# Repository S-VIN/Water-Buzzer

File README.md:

# Water-Buzzer
 гит проекта системы оповещения о сухости почвы.

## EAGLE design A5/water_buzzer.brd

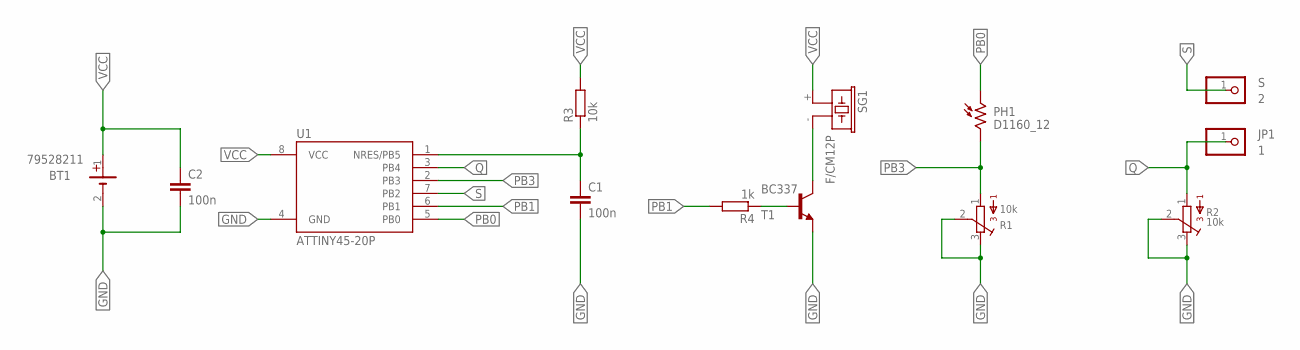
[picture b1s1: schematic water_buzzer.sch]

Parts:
BT1: 79528211
C1, C2: 100n; C5B2.5
JP1: 1; 1X01
PH1: D1160_12; D11XX
R1, R2: 10k; 3362H
R3: 10k; 0204/7
R4: 1k; 0204/7
S: 2; 1X01
SG1: F/CM12P
T1: BC337; TO92
U1: ATTINY45-20P; PDIP08_300MIL

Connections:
GND: BT1.2 (-), C1.2, C2.2, R1.2, R1.3, R2.2, R2.3, T1.1 (E), U1.4 (GND)
unnamed: C1.1, R3.1, U1.1 (NRES/PB5)
unnamed: SG1.- (2), T1.3 (C)
unnamed: R4.1, T1.2 (B)
PB0: PH1.1, U1.5 (PB0)
PB1: R4.2, U1.6 (PB1)
PB3: PH1.2, R1.1, U1.2 (PB3)
Q: JP1.1, R2.1, U1.3 (PB4)
S: S.1, U1.7 (PB2)
VCC: BT1.1 (+), C2.1, R3.2, SG1.+ (1), U1.8 (VCC)

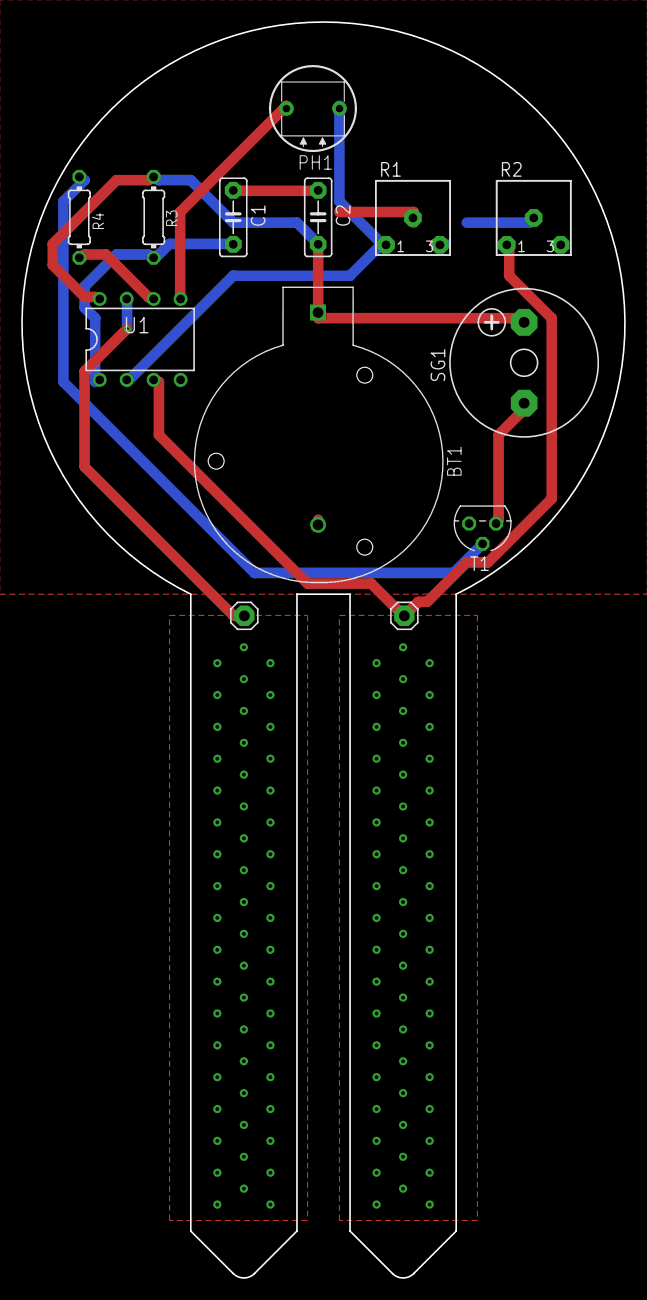
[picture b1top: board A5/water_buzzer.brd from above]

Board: 4 copper layers, 56.8 x 118.3 mm, 13 parts (0 on the bottom side), 10 nets.

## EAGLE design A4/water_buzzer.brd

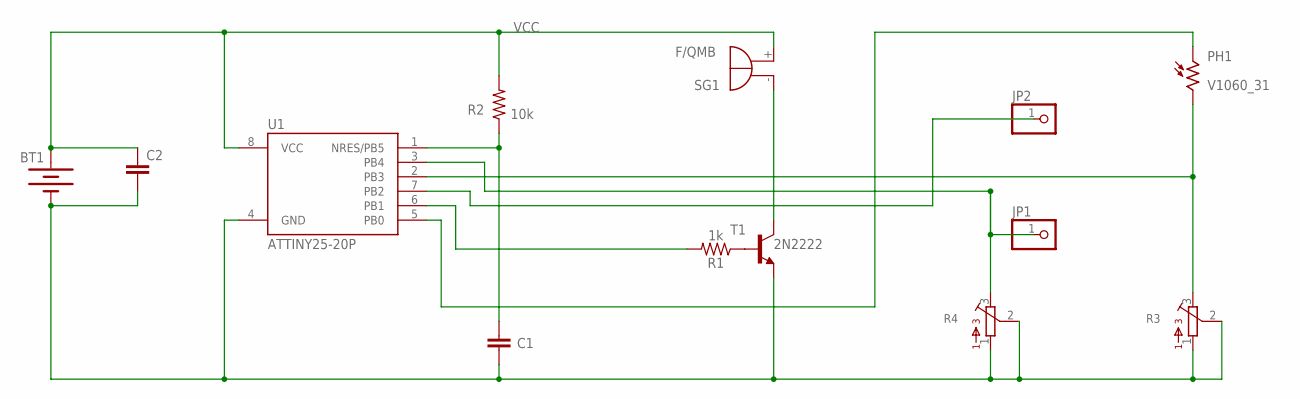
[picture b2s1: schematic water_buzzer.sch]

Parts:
BT1: BATTERY-20MM_PTH; BATTCOM_20MM_PTH
C1, C2: C5/2.5; C5B2.5
JP1, JP2: PINHD-1X1; 1X01
PH1: V1060_31; TO-5_V10
R1: 1k; AXIAL-0.3
R2: 10k; AXIAL-0.3
R3, R4: 3362R
SG1: F/QMB
T1: 2N2222; TO92-EBC-OVAL
U1: ATTINY25-20P; PDIP08_300MIL

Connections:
unnamed: BT1.1 (+), C2.1, R2.P$2 (2), SG1.+ (-), U1.8 (VCC)
unnamed: BT1.2 (-), C1.1, C2.2, R3.1, R3.2, R4.1, R4.2, T1.E, U1.4 (GND)
unnamed: C1.2, R2.P$1 (1), U1.1 (NRES/PB5)
unnamed: JP2.1, U1.7 (PB2)
unnamed: R1.P$1 (1), T1.B
unnamed: JP1.1, R4.3, U1.3 (PB4)
unnamed: SG1.- (+), T1.C
unnamed: R1.P$2 (2), U1.6 (PB1)
unnamed: PH1.1, U1.5 (PB0)
unnamed: PH1.2, R3.3, U1.2 (PB3)

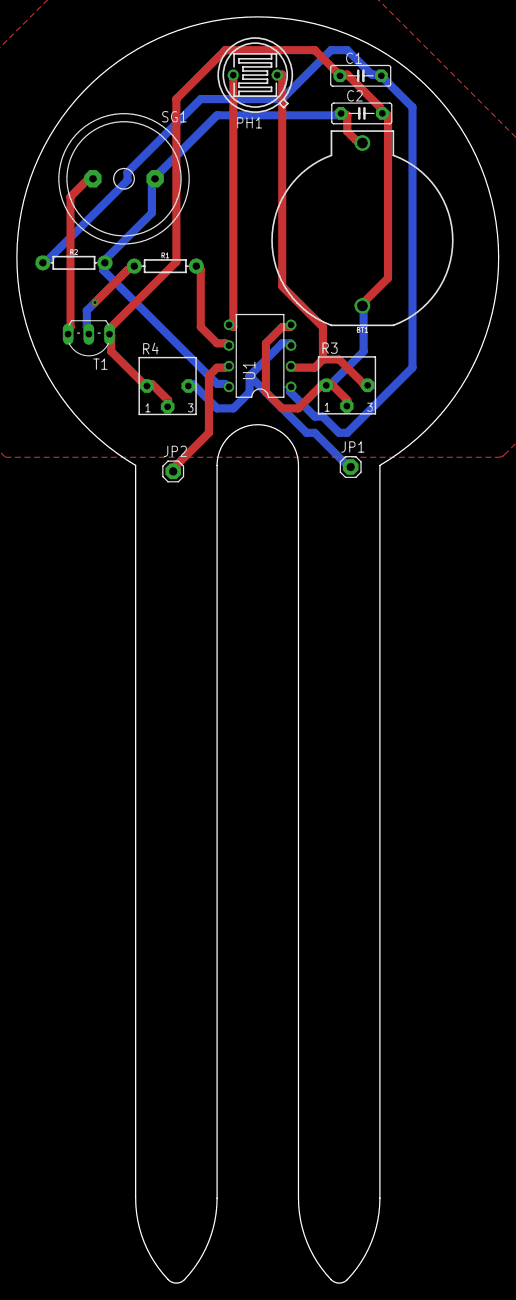
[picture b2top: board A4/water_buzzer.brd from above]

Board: 2 copper layers, 59.2 x 155.5 mm, 13 parts (0 on the bottom side), 10 nets.

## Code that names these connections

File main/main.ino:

inline void SetupPins(){
  //         x              - Биты отвечают за назначение пинов
  //         |x             - 1 - OUTPUT; 0 - INPUT
  //         ||DDB5         - PB5
  //         |||DDB4        - PB4
  //         ||||DDB3       - PB3
  //         |||||DDB2      - PB2
  //         ||||||DDB1     - PB1
  //         |||||||DDB0    - PB0
  //         ||||||||
  DDRB = 0b00111010;
}

/*inline void SetupWatchdog(){

  // WDP3  WDP2  WDP1  WDP0 - отвечают за время срабатывания watchdog
  //  0      0     0     0  - 16ms
  //  0      1     0     0  - 25ms
  //  0      1     1     0  - 1s
  //  0      1     1     1  - 2s
  //  1      0     0     0  - 4s
  //  1      0     0     1  - 8s - maximum
  
  // WDE  WDIE  - отвечают за режимы watchdog
  //  0    0    - none
  //  0    1    - interrupt mode
  //  1    0    - reset mode
  //  1    1    - interrupt reset mode

  //          WDIF            - устнавливается 1 когда вотчдог таймер срабатывает (в режиме прерываний)
  //          |WDIE           - меняет режимы 
  //          ||WDP3          - 
  //          |||WDCE         - необходимо установить еденицу когда WDE - 0  
  //          ||||WDE         - включение watchdog
  //          |||||WDP2       - 
  //          ||||||WDP1      - 
  //          |||||||WDP0     - 
  //          ||||||||
  //WDTCR = 0b00000000;
  
  WDTCR |= (0 << WDIE);
  WDTCR |= (1 << WDE);
  WDTCR |= (1 << WDP3);
  WDTCR |= (0 << WDP2);
  WDTCR |= (0 << WDP1);
  WDTCR |= (0 << WDP0);
  
}*/
#include <avr/io.h>
#include <avr/wdt.h>
#include <util/delay.h>
#include <avr/sleep.h>
#include <avr/power.h>
#include <avr/interrupt.h>
#include <EEPROM.h>



int n = 126;                         //количество ячеек памяти в EEPROM attiny25 - 128; attiny45 - 256; attiny85 - 512 



ISR (WDT_vect) {                      //обработка прерывания watchdog
  if (EEPROM[0] >= 4){
      EEPROM[0] = 0;
    ADCSRA = (1 << ADEN) ;              //включение АЦП (в POWER_DOWN_MODE выключен)
    digitalWrite(3, HIGH);
    digitalWrite(1, HIGH);
    if ((analogRead(2) < 300)/* && (analogRead(0) > 600)*/){
      digitalWrite(4, HIGH);
      _delay_ms(100);
      digitalWrite(4, LOW);  
    }
    ADCSRA = (0 << ADEN) ;            //выключение АЦП(потребляет о.3 мА)
    digitalWrite(3, HIGH);
    digitalWrite(1, HIGH);
    WDTCR |= (1 << WDIE);             // разрешаем прерывания по watchdog. Иначе будет ресет.
  }
  EEPROM[0] = EEPROM[0] + 1;
}

int main(void)
{
    _delay_ms(100);
    //a.clear();
    pinMode(0, INPUT);
    pinMode(1, OUTPUT);
    pinMode(2, INPUT);
    pinMode(3, OUTPUT);
    pinMode(4, OUTPUT);


    wdt_reset();          
    wdt_enable(WDTO_2S);            //watch_dog инициализация 8s timer
    
    WDTCR |= (1 << WDIE);           // разрешаем прерывания по ватчдогу. Иначе будет резет.
    sei();                          //установить флаг глобального прерывания http://www.gaw.ru/html.cgi/txt/doc/micros/avr/asm/sei.htm
    MCUCR=0x30;                     // настраиваем режим энергосбережения. POWER_DOWN_MODE
   
    while(1) {
      sleep_mode();
    }
}

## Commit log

2019-07-09 Create EEPROM_loopAlgoritm.ino
    алгоритм кольцевого буфера для долгой работы EEPROM
2019-07-09 09ю07
2019-07-12 atmel
2019-07-12 altium
2019-07-15 main
2019-07-16 dhjlt dct
2019-07-18 RBuf
2019-07-18 size_t => uint8_t
2019-07-19 elfkbk
2019-07-19 почти все нормально
2019-07-22 просто так
2019-08-28 big commit
2019-12-16 newCommit

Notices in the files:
parts and their libraries:
SparkFun-Batteries: Licensing: Creative Commons ShareAlike 4.0 International - https://creativecommons.org/licenses/by-sa/4.0
